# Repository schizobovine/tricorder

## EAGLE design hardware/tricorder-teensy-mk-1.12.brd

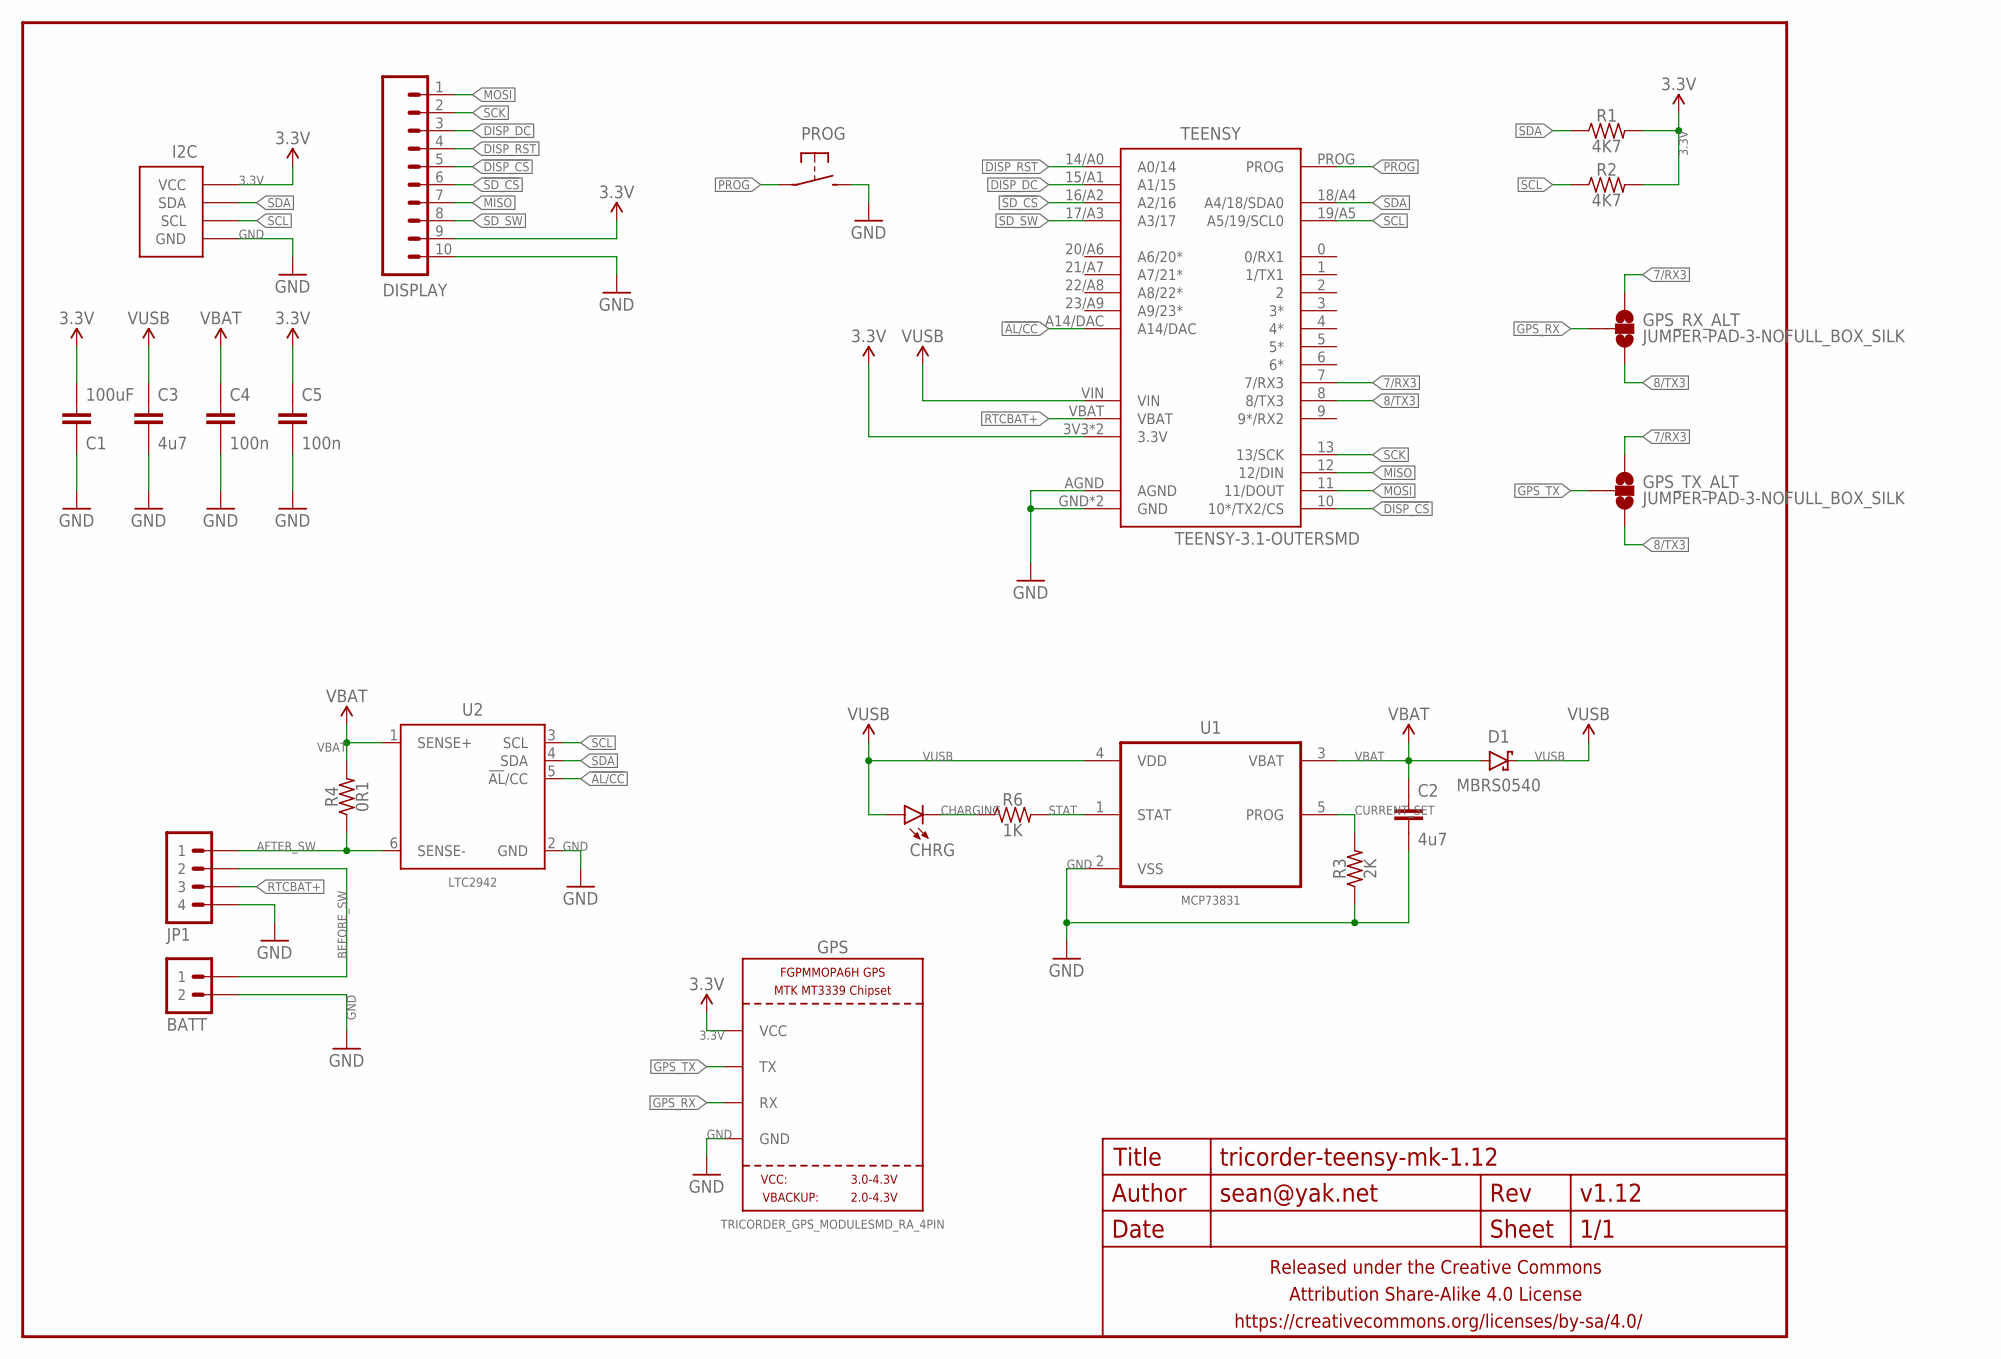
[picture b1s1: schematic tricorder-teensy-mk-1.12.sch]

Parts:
BATT: M02JST-2MM-SMT; JST-2-SMD
C1: 100uF; C1210
C2, C3: 4u7; C0603-TIGHTER
C4, C5: 100n; C0603-TIGHTER
CHRG: LED0603-TIGHT; LED-0603-TIGHT
D1: MBRS0540; SOD123-SCHOTTKY
DISPLAY: M10SMD_RA_2MM; 1X10_SMD_RA_MALE
FRAME1: FRAME-LETTERNO_PACKAGE; DUMMY
GPS: TRICORDER_GPS_MODULESMD_RA_4PIN; TRICORDER_GPS_MODULE_RA_CONN_SMD_4PIN
GPS_RX_ALT: JUMPER-PAD-3-NOFULL_BOX_SILK; PAD-JUMPER-3-NO_YES_SILK_FULL_BOX
GPS_TX_ALT: JUMPER-PAD-3-NOFULL_BOX_SILK; PAD-JUMPER-3-NO_YES_SILK_FULL_BOX
I2C: M04-I2CSMD_2MM_RA; 1X04_SMD_RA_2MM_I2C
JP1: M04SMD_RA_2MM; 1X04_SMD_RA_2MM
PROG: SPST-NO-TACTCK-PTS840-GK; TACTILE-SMD-CK-PTS840-GK
R1, R2: 4K7; R0603-TIGHTER
R3: 2K; R0603-TIGHTER
R4: 0R1; R0805-TIGHTER
R6: 1K; R0603-TIGHTER
TEENSY: TEENSY-3.1-OUTERSMD; TEENSY-3.1_SMT_BOTTOM_OUTERONLY
U1: MCP73831; SOT95P280X145-5N
U2: LTC2942; DFN200X300X50-7N

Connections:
3.3V: C1.2, C5.1, DISPLAY.9, GPS.VCC, I2C.VCC, R1.2, R2.2, TEENSY.3V3 (3.3V), TEENSY.3V3@1 (3.3V)
7/RX3: GPS_RX_ALT.1, GPS_TX_ALT.1, TEENSY.7 (7/RX3)
8/TX3: GPS_RX_ALT.3, GPS_TX_ALT.3, TEENSY.8 (8/TX3)
!AL/CC: TEENSY.A14/DAC, U2.5 (!AL!/CC)
!DISP_CS: DISPLAY.5, TEENSY.10 (10*/TX2/CS)
!SD_CS: DISPLAY.6, TEENSY.16/A2 (A2/16)
AFTER_SW: JP1.1, R4.1, U2.6 (SENSE-)
BEFORE_SW: BATT.2 (1), JP1.2
CHARGING: CHRG.C, R6.1
CURRENT_SET: R3.2, U1.5 (PROG)
DISP_DC: DISPLAY.3, TEENSY.15/A1 (A1/15)
DISP_RST: DISPLAY.4, TEENSY.14/A0 (A0/14)
GND: BATT.1 (2), C1.1, C2.2, C3.2, C4.2, C5.2, DISPLAY.10, GPS.GND, I2C.GND, JP1.4, PROG.3 (2), PROG.4 (2), R3.1, TEENSY.AGND, TEENSY.GND, TEENSY.GND@1 (GND), U1.2 (VSS), U2.2 (GND)
GPS_RX: GPS.RX, GPS_RX_ALT.2
GPS_TX: GPS.TX, GPS_TX_ALT.2
MISO: DISPLAY.7, TEENSY.12 (12/DIN)
MOSI: DISPLAY.1, TEENSY.11 (11/DOUT)
PROG: PROG.1, PROG.2 (1), TEENSY.PROG
RTCBAT+: JP1.3, TEENSY.VBAT
SCK: DISPLAY.2, TEENSY.13 (13/SCK)
SCL: I2C.SCL, R2.1, TEENSY.19/A5 (A5/19/SCL0), U2.3 (SCL)
SDA: I2C.SDA, R1.1, TEENSY.18/A4 (A4/18/SDA0), U2.4 (SDA)
SD_SW: DISPLAY.8, TEENSY.17/A3 (A3/17)
STAT: R6.2, U1.1 (STAT)
VBAT: C2.1, C4.1, D1.A, R4.2, U1.3 (VBAT), U2.1 (SENSE+)
VUSB: C3.1, CHRG.A, D1.C, TEENSY.VIN, U1.4 (VDD)

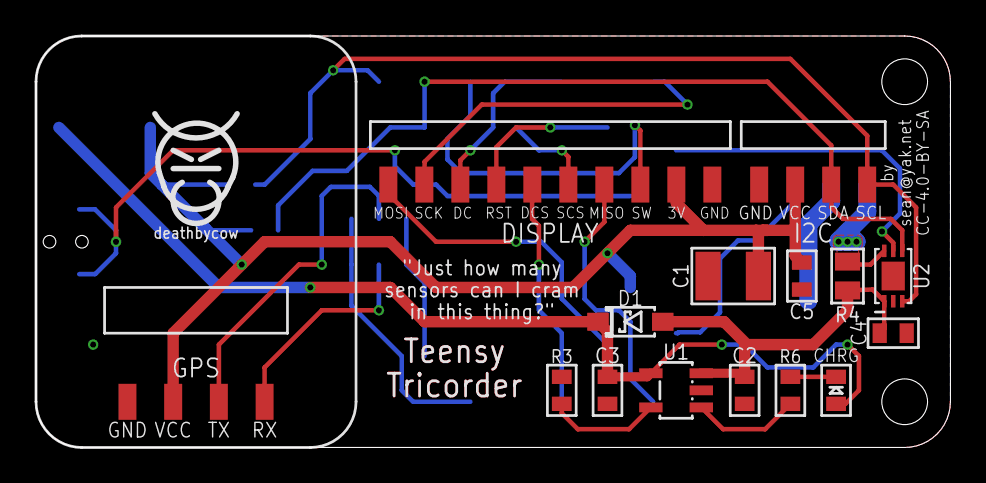
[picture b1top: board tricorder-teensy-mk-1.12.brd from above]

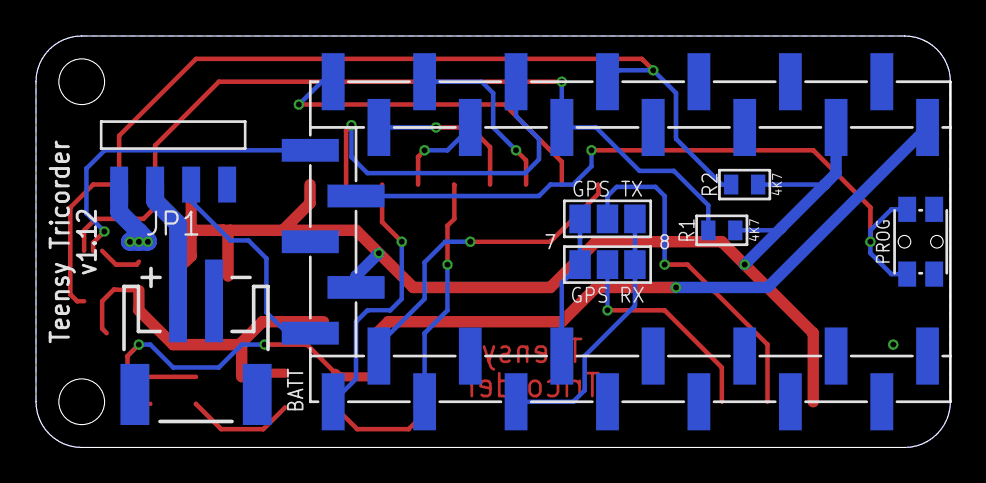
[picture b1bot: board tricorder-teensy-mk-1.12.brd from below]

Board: 2 copper layers, 50.8 x 22.9 mm, 25 parts (7 on the bottom side), 26 nets.

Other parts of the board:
U$1: COW_SMALL

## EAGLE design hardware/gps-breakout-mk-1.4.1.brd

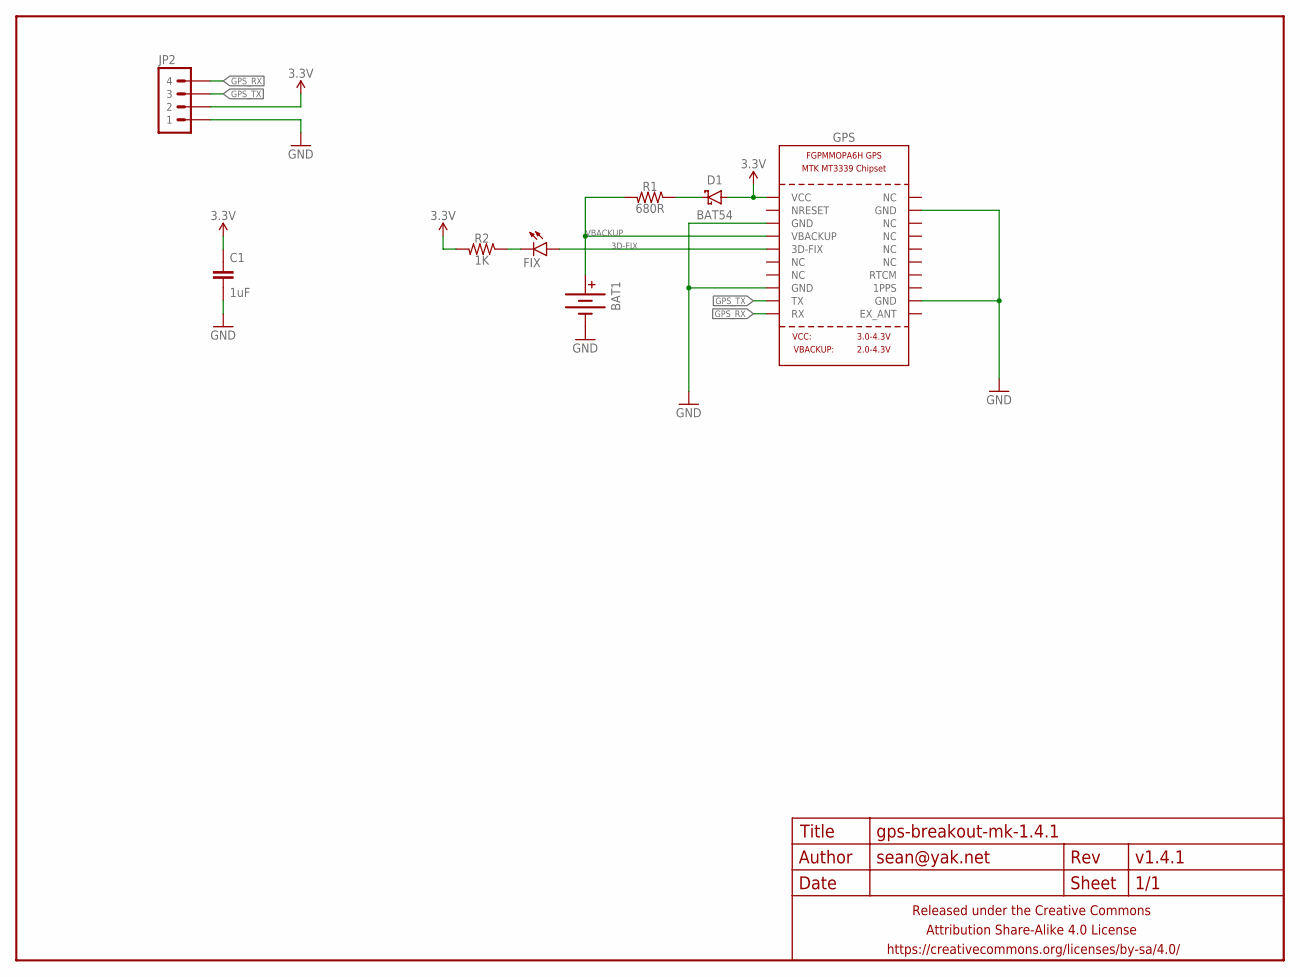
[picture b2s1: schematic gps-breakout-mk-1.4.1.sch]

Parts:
BAT1: BATTERYML414; BATTCON_4.8MM
C1: 1uF; C0603-TIGHTER
D1: BAT54; SOD323-SCHOTTKY
FIX: LED0603-TIGHT; LED-0603-TIGHT
FRAME1: FRAME-LETTERNO_PACKAGE; DUMMY
GPS: GPS_FGPMMOPA6H; FGPMMOPA6H
JP2: M04SMD-FEMALE-DUAL; 1X04-SMD-FEMALE-RA-DUAL
R1: 680R; R0603-TIGHTER
R2: 1K; R0603-TIGHTER

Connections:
3.3V: C1.1, D1.A, GPS.P$1 (VCC), JP2.P$2 (2), JP2.P$2_1 (2), R2.2
3D-FIX: FIX.A, GPS.P$5 (3D-FIX)
GND: BAT1.-, C1.2, GPS.P$3 (GND), GPS.P$8 (GND), GPS.P$12 (GND), GPS.P$19 (GND), JP2.P$1 (1), JP2.P$1_1 (1)
GPS_RX: GPS.P$10 (RX), JP2.P$4 (4), JP2.P$4_1 (4)
GPS_TX: GPS.P$9 (TX), JP2.P$3 (3), JP2.P$3_1 (3)
unnamed: D1.C, R1.1
unnamed: FIX.C, R2.1
VBACKUP: BAT1.A1 (+), BAT1.A2 (+), GPS.P$4 (VBACKUP), R1.2

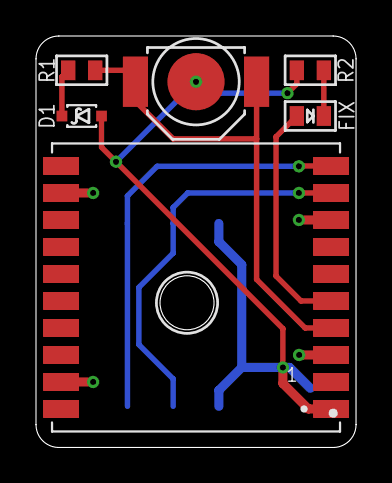
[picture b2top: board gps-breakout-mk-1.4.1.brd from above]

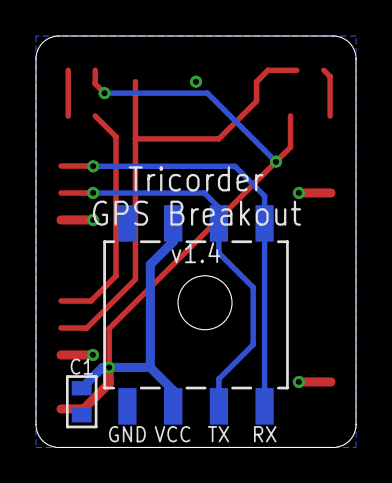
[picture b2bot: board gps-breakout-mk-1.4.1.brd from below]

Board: 2 copper layers, 17.8 x 22.9 mm, 9 parts (2 on the bottom side), 8 nets.

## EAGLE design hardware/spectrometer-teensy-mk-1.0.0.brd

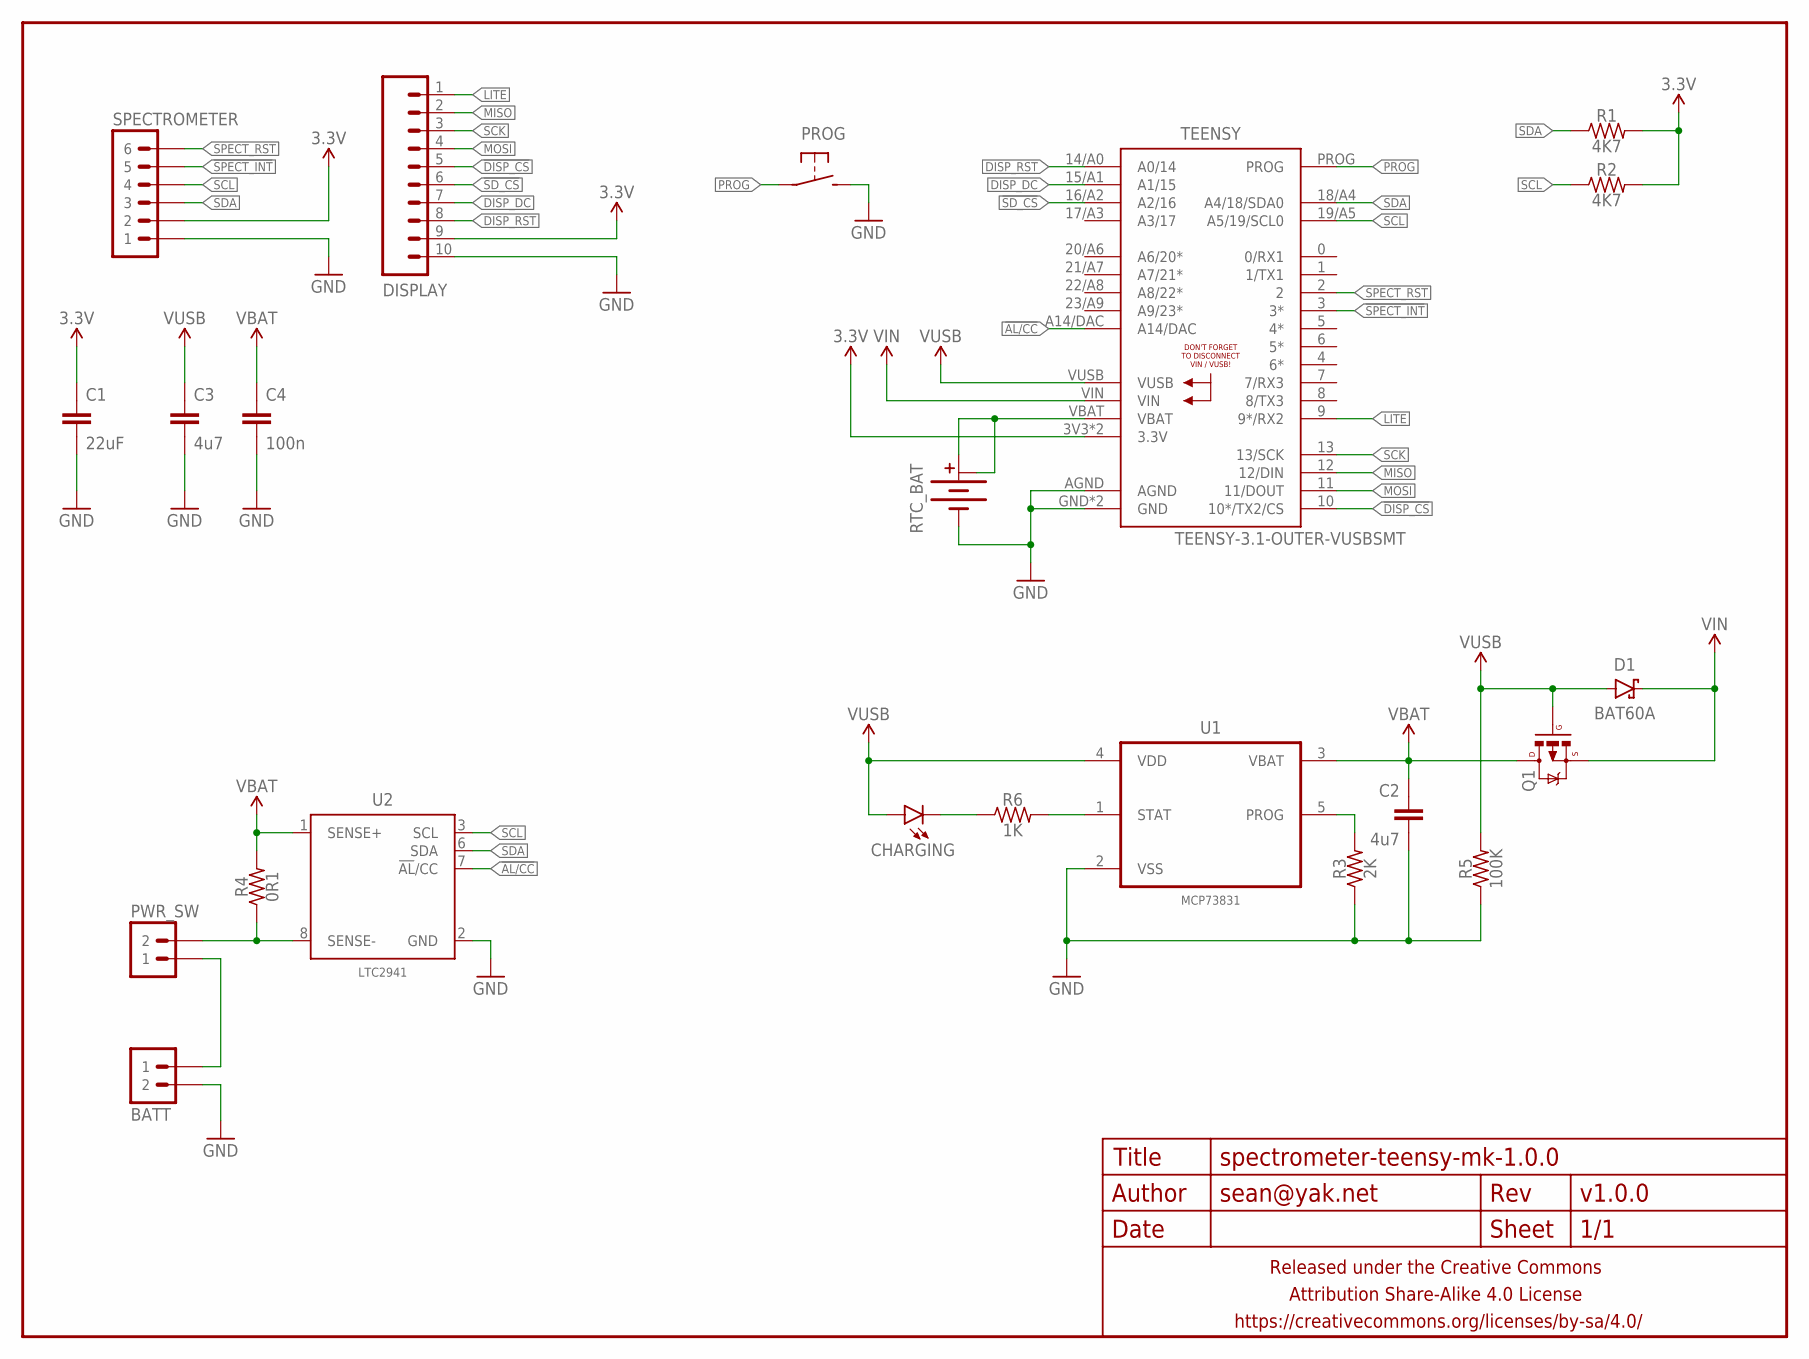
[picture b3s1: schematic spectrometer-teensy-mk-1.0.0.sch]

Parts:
BATT: M02JST-2MM-SMT; JST-2-SMD
C1: 22uF; C0805-TIGHTER
C2, C3: 4u7; C0603-TIGHTER
C4: 100n; C0603-TIGHTER
CHARGING: LED0603-TIGHT; LED-0603-TIGHT
D1: BAT60A; SOD123-SCHOTTKY
DISPLAY: M10SMD_RA_2MM; 1X10_SMD_RA_MALE
FRAME1: FRAME-LETTERNO_PACKAGE; DUMMY
PROG: SPST-NO-TACTCK-PTS840-GK; TACTILE-SMD-CK-PTS840-GK
PWR_SW: M02JST-2MM-SMT; JST-2-SMD
Q1: MOSFET-PCHANNELSOT-23; SOT23
R1, R2: 4K7; R0603-TIGHTER
R3: 2K; R0603-TIGHTER
R4: 0R1; R0603-TIGHTER
R5: 100K; R0603-TIGHTER
R6: 1K; R0603-TIGHTER
RTC_BAT: BATTERY-COINCR1225_SMD_SMALLER; BATTCON_12MM_SMD
SPECTROMETER: M06SMD-2MM-RA; 1X06_SMD_RA_2MM
TEENSY: TEENSY-3.1-OUTER-VUSBSMT; TEENSY-3.1_SMT_BOTTOM_OUTERMOSTLY_VUSB
U1: MCP73831; SOT95P280X145-5N
U2: LTC2941; MSOP-8

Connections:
3.3V: C1.1, DISPLAY.9, R1.2, R2.2, SPECTROMETER.2, TEENSY.3V3 (3.3V), TEENSY.3V3@1 (3.3V)
!AL/CC: TEENSY.A14/DAC, U2.7 (!AL!/CC)
!DISP_CS: DISPLAY.5, TEENSY.10 (10*/TX2/CS)
!SD_CS: DISPLAY.6, TEENSY.16/A2 (A2/16)
!SPECT_INT: SPECTROMETER.5, TEENSY.3 (3*)
DISP_DC: DISPLAY.7, TEENSY.15/A1 (A1/15)
DISP_RST: DISPLAY.8, TEENSY.14/A0 (A0/14)
GND: BATT.1 (2), C1.2, C2.2, C3.2, C4.2, DISPLAY.10, PROG.3 (2), PROG.4 (2), R3.1, R5.1, RTC_BAT.-, SPECTROMETER.1, TEENSY.AGND, TEENSY.GND, TEENSY.GND@1 (GND), U1.2 (VSS), U2.2 (GND)
LITE: DISPLAY.1, TEENSY.9 (9*/RX2)
MISO: DISPLAY.2, TEENSY.12 (12/DIN)
MOSI: DISPLAY.4, TEENSY.11 (11/DOUT)
unnamed: R6.2, U1.1 (STAT)
unnamed: CHARGING.C, R6.1
unnamed: BATT.2 (1), PWR_SW.2 (1)
unnamed: R3.2, U1.5 (PROG)
unnamed: PWR_SW.1 (2), R4.1, U2.8 (SENSE-)
unnamed: RTC_BAT.+@1 (+), RTC_BAT.+@2 (+1), TEENSY.VBAT
PROG: PROG.1, PROG.2 (1), TEENSY.PROG
SCK: DISPLAY.3, TEENSY.13 (13/SCK)
SCL: R2.1, SPECTROMETER.4, TEENSY.19/A5 (A5/19/SCL0), U2.3 (SCL)
SDA: R1.1, SPECTROMETER.3, TEENSY.18/A4 (A4/18/SDA0), U2.6 (SDA)
SPECT_RST: SPECTROMETER.6, TEENSY.2
VBAT: C2.1, C4.1, Q1.3 (D), R4.2, U1.3 (VBAT), U2.1 (SENSE+)
VIN: D1.C, Q1.2 (S), TEENSY.VIN
VUSB: C3.1, CHARGING.A, D1.A, Q1.1 (G), R5.2, TEENSY.VUSB, U1.4 (VDD)

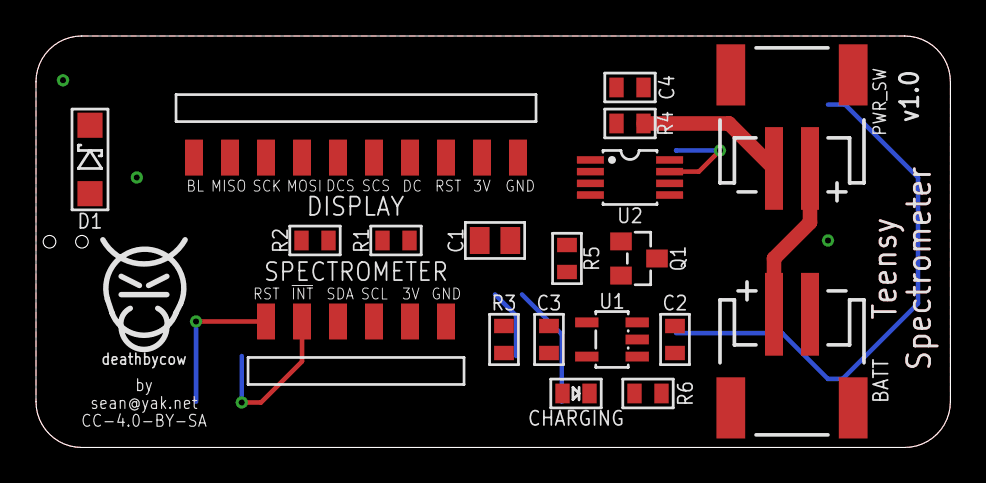
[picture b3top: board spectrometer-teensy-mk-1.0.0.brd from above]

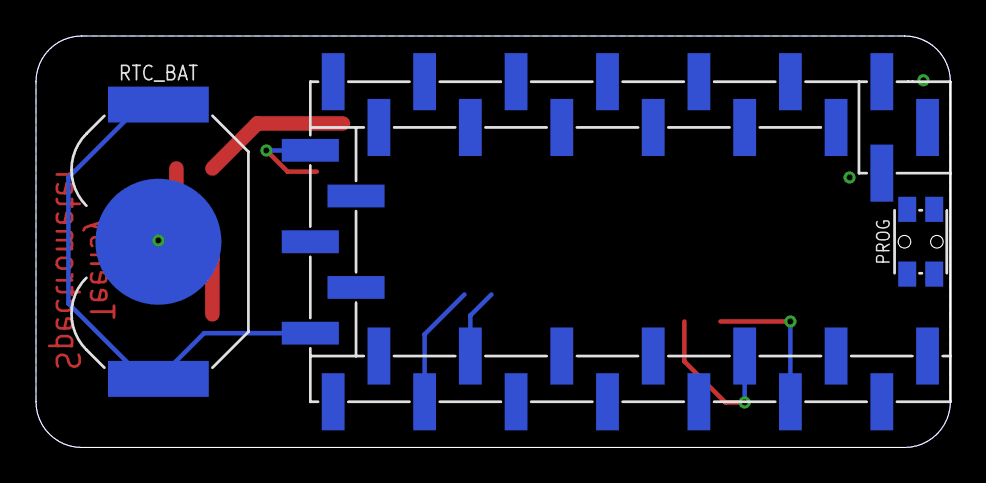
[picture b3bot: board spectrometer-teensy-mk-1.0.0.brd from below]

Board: 2 copper layers, 50.8 x 22.9 mm, 24 parts (2 on the bottom side), 25 nets.

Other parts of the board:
U$1: COW_SMALL

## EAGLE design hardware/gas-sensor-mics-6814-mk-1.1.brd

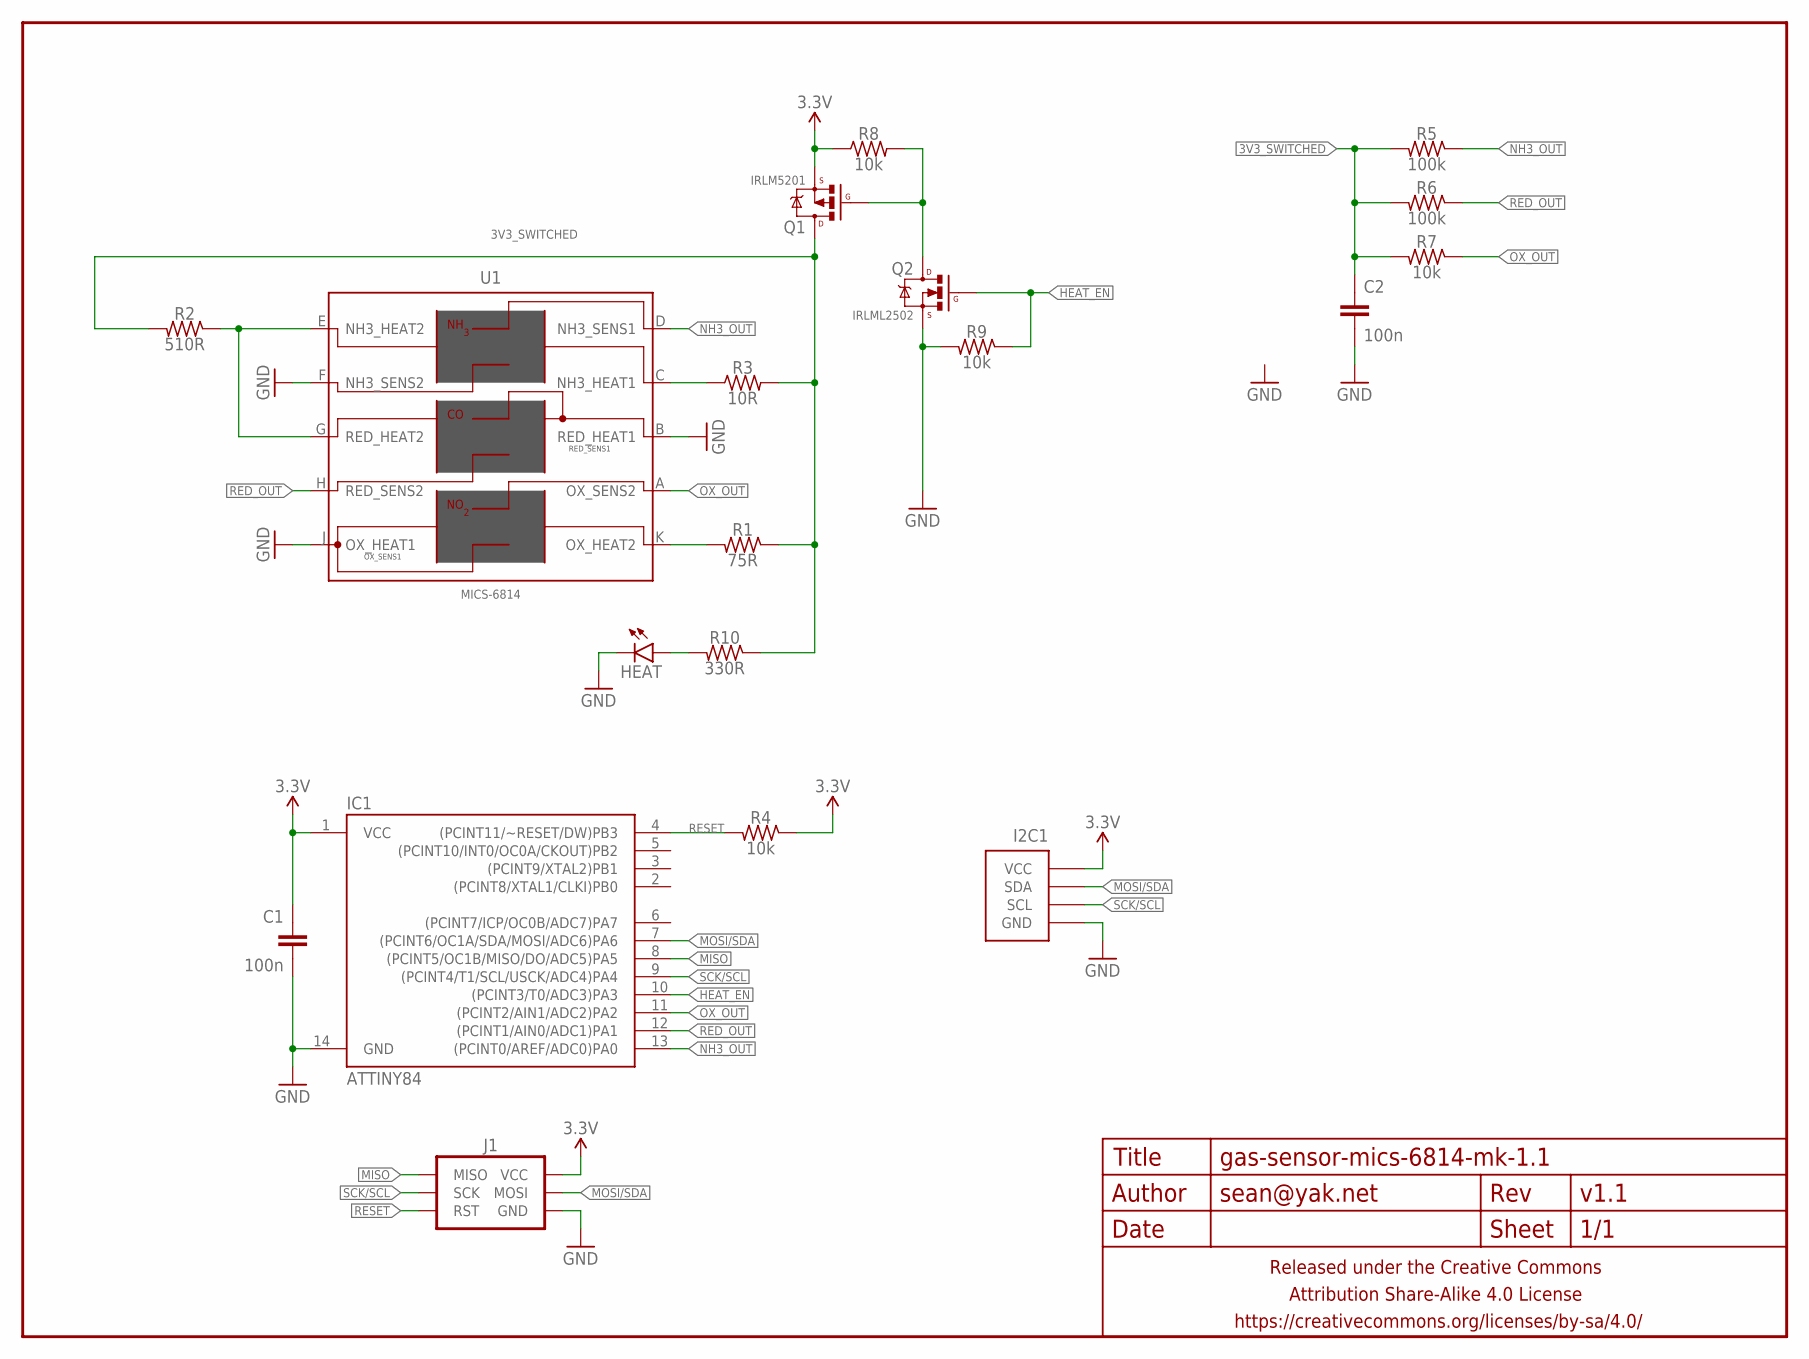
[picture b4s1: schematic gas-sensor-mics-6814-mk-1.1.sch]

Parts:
C1, C2: 100n; C0603-TIGHTER
FRAME1: FRAME-LETTERNO_PACKAGE; DUMMY
HEAT: LED0603-TIGHT; LED-0603-TIGHT
I2C1: M04-I2CPTH-0.1IN-CENTERED; 1X04-PTH-VERT-I2C-CENTERED
IC1: ATTINY84; SO14
J1: AVR_SPI_PRG_6SMD_TEST_POINTS; 2X3_SMD_TEST_POINTS
Q1: IRLM5201; SOT23
Q2: IRLML2502; SOT23
R1: 75R; R0603-TIGHTER
R2: 510R; R0603-TIGHTER
R3: 10R; R0603-TIGHTER
R4, R7, R8, R9: 10k; R0603-TIGHTER
R5, R6: 100k; R0603-TIGHTER
R10: 330R; R0603-TIGHTER
U1: MICS-6814; MICS-10-PIN

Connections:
3.3V: C1.1, I2C1.VCC, IC1.1 (VCC), J1.2 (VCC), Q1.2 (S), R4.1, R8.1
3V3_SWITCHED: C2.1, Q1.3 (D), R1.1, R2.2, R3.2, R5.2, R6.2, R7.2, R10.1
GND: C1.2, C2.2, HEAT.C, I2C1.GND, IC1.14 (GND), J1.6 (GND), Q2.2 (S), R9.2, U1.B (RED_HEAT1), U1.F (NH3_SENS2), U1.J (OX_HEAT1)
HEAT_EN: IC1.10 ((PCINT3/T0/ADC3)PA3), Q2.1 (G), R9.1
MISO: IC1.8 ((PCINT5/OC1B/MISO/DO/ADC5)PA5), J1.1 (MISO)
MOSI/SDA: I2C1.SDA, IC1.7 ((PCINT6/OC1A/SDA/MOSI/ADC6)PA6), J1.4 (MOSI)
unnamed: R2.1, U1.E (NH3_HEAT2), U1.G (RED_HEAT2)
unnamed: R1.2, U1.K (OX_HEAT2)
unnamed: R3.1, U1.C (NH3_HEAT1)
unnamed: Q1.1 (G), Q2.3 (D), R8.2
unnamed: HEAT.A, R10.2
NH3_OUT: IC1.13 ((PCINT0/AREF/ADC0)PA0), R5.1, U1.D (NH3_SENS1)
OX_OUT: IC1.11 ((PCINT2/AIN1/ADC2)PA2), R7.1, U1.A (OX_SENS2)
RED_OUT: IC1.12 ((PCINT1/AIN0/ADC1)PA1), R6.1, U1.H (RED_SENS2)
RESET: IC1.4 ((PCINT11/~RESET/DW)PB3), J1.5 (RST), R4.2
SCK/SCL: I2C1.SCL, IC1.9 ((PCINT4/T1/SCL/USCK/ADC4)PA4), J1.3 (SCK)

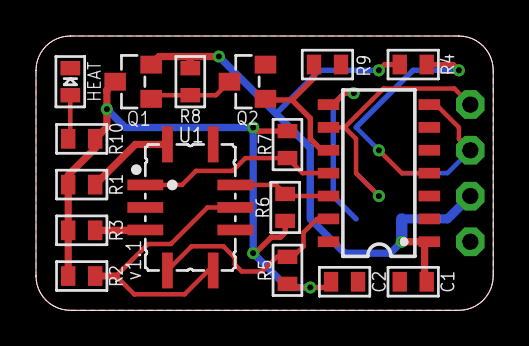
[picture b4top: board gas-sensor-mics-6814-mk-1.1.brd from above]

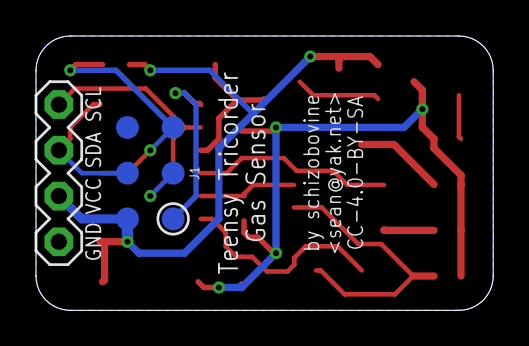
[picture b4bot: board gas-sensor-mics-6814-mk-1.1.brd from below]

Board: 2 copper layers, 25.4 x 15.2 mm, 20 parts (2 on the bottom side), 16 nets.

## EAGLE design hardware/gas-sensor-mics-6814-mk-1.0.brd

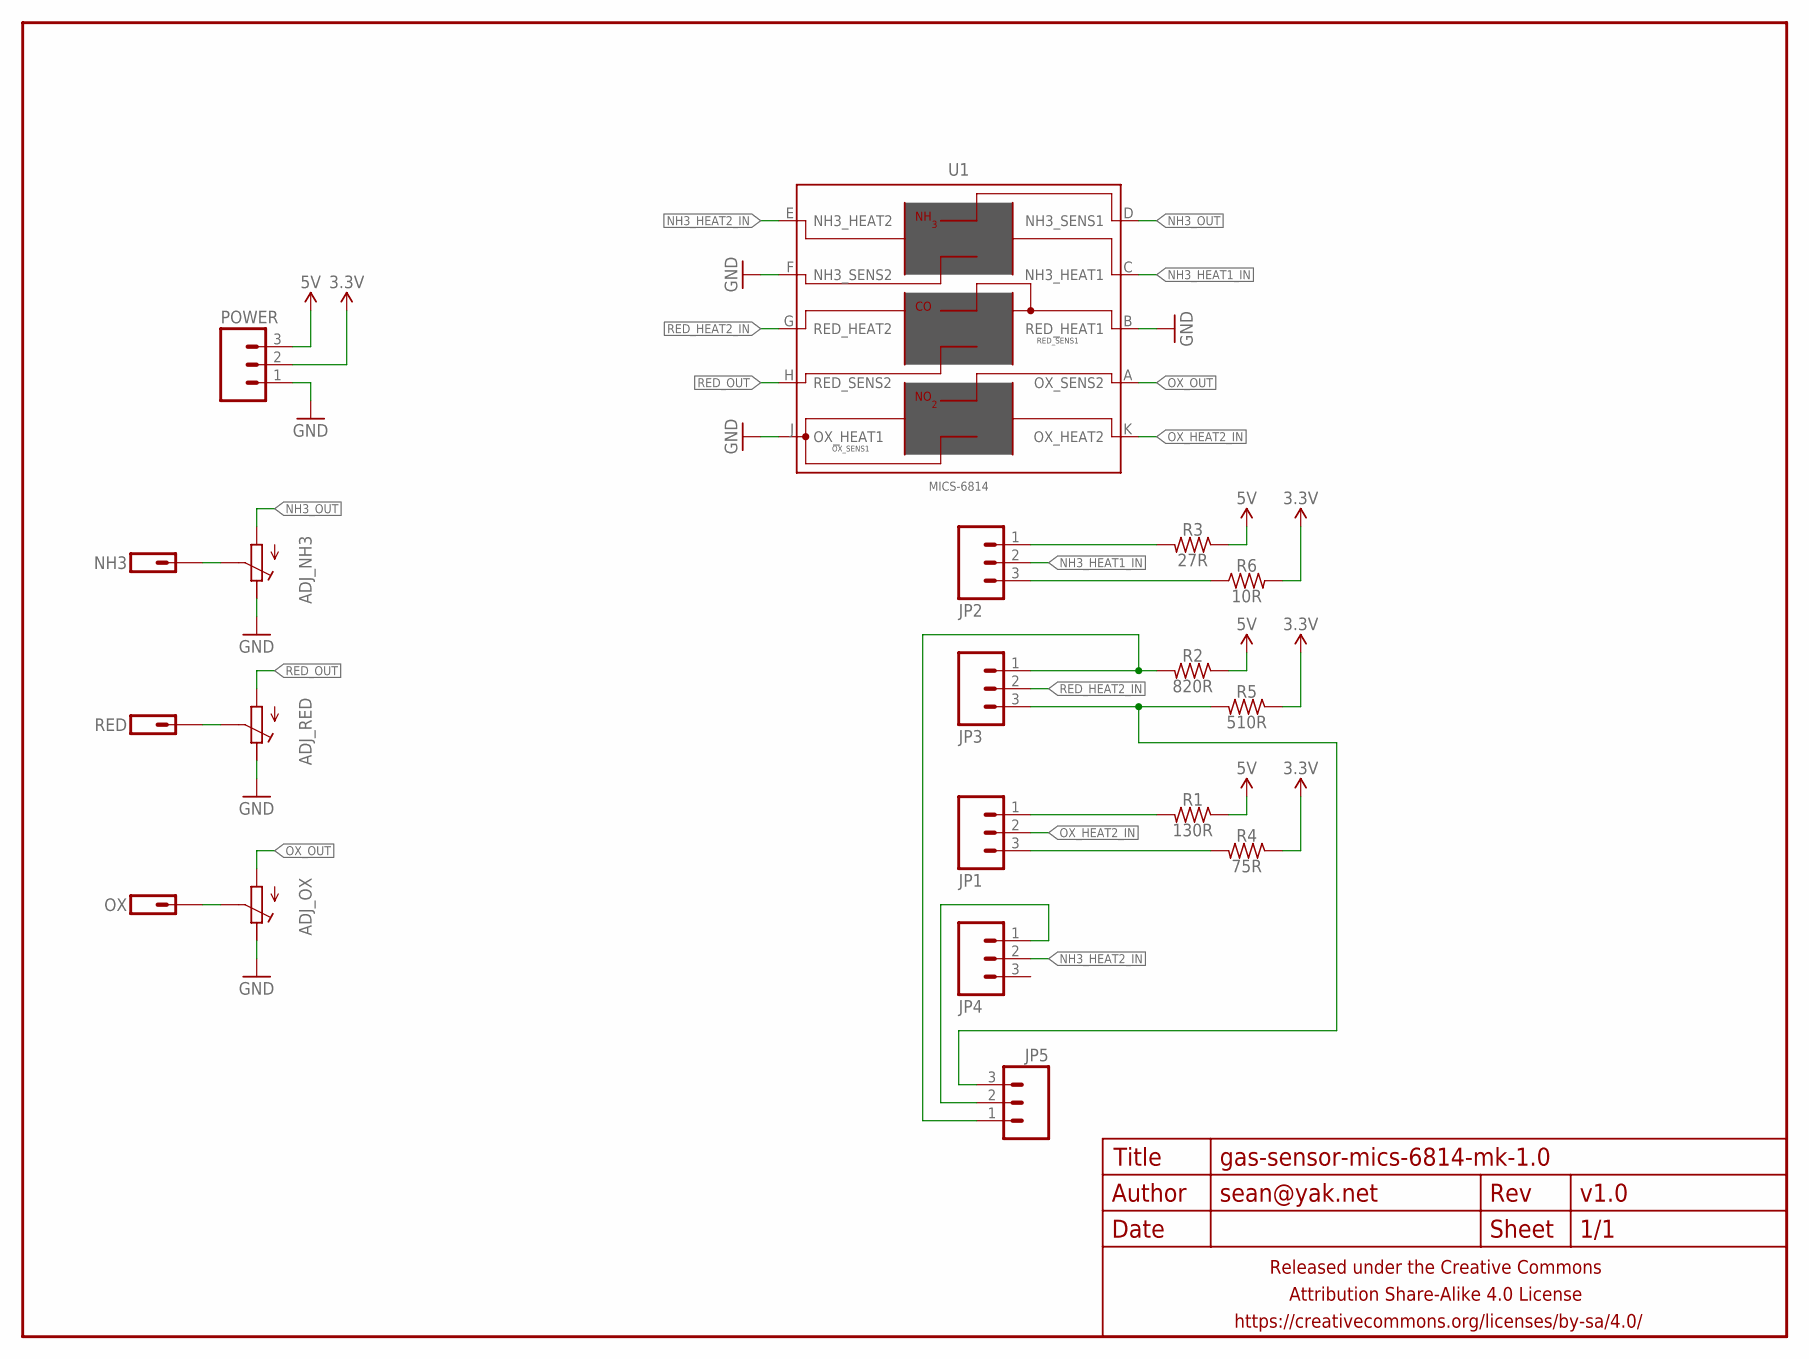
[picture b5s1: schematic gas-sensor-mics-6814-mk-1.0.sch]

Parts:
ADJ_NH3: POTENTIOMETEREVM3Y; EVM3Y
ADJ_OX: POTENTIOMETEREVM3Y; EVM3Y
ADJ_RED: POTENTIOMETEREVM3Y; EVM3Y
FRAME1: FRAME-LETTERNO_PACKAGE; DUMMY
JP1, JP2, JP3, JP4, JP5: M03PTH-CENTERED; 1X03-CENTERED
NH3: M01PTH-2MM-OFFSET; 1X01_2MM_OFFSET
OX: M01PTH-2MM-OFFSET; 1X01_2MM_OFFSET
POWER: M03PTH-CENTERED; 1X03-CENTERED
R1: 130R; R0603-TIGHTER
R2: 820R; R0603-TIGHTER
R3: 27R; R0603-TIGHTER
R4: 75R; R0603-TIGHTER
R5: 510R; R0603-TIGHTER
R6: 10R; R0603-TIGHTER
RED: M01PTH-2MM-OFFSET; 1X01_2MM_OFFSET
U1: MICS-6814; MICS-10-PIN

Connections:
3.3V: POWER.2, R4.1, R5.1, R6.2
5V: POWER.3, R1.1, R2.1, R3.1
GND: ADJ_NH3.E, ADJ_OX.E, ADJ_RED.E, POWER.1, U1.B (RED_HEAT1), U1.F (NH3_SENS2), U1.J (OX_HEAT1)
unnamed: JP2.1, R3.2
unnamed: ADJ_NH3.S, NH3.1
unnamed: ADJ_RED.S, RED.1
unnamed: ADJ_OX.S, OX.1
unnamed: JP1.1, R1.2
unnamed: JP1.3, R4.2
unnamed: JP2.3, R6.1
unnamed: JP3.3, JP5.3, R5.2
unnamed: JP3.1, JP5.1, R2.2
unnamed: JP4.1, JP5.2
NH3_HEAT1_IN: JP2.2, U1.C (NH3_HEAT1)
NH3_HEAT2_IN: JP4.2, U1.E (NH3_HEAT2)
NH3_OUT: ADJ_NH3.A, U1.D (NH3_SENS1)
OX_HEAT2_IN: JP1.2, U1.K (OX_HEAT2)
OX_OUT: ADJ_OX.A, U1.A (OX_SENS2)
RED_HEAT2_IN: JP3.2, U1.G (RED_HEAT2)
RED_OUT: ADJ_RED.A, U1.H (RED_SENS2)

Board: 2 copper layers, 20 parts (0 on the bottom side), 20 nets, no tracks yet.

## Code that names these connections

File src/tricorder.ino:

/*
 * tricorder.ino
 *
 * Adafruit Feather-based, Bluetooth-enabled sensor thingy.
 *
 * Author: Sean Caulfield <sean@yak.net>
 * License: GPL v2.0
 *
 */

#include <Arduino.h>
#include <SPI.h>
#include <Wire.h>
#include <SD.h>

#include <Adafruit_GFX.h>
#include <Adafruit_SSD1351.h>
#include <Adafruit_BLE.h>
#include <Adafruit_BluefruitLE_SPI.h>

#include <Adafruit_Sensor.h>
#include <Adafruit_BMP280.h>
#include <Adafruit_BNO055.h>
#include <Adafruit_MLX90614.h>
#include <Adafruit_SHT31.h>
#include <Adafruit_TCS34725.h>
#include <Adafruit_TSL2591.h>
#include <Adafruit_VEML6070.h>

#define BATT_DIV_PIN   A7

#define SD_CARDDETECT  A1
#define SD_CS          A2

#define DISP_CS        A3
#define DISP_DC        A4
#define DISP_RST       A5

#define BLE_CS         8
#define BLE_IRQ        7
#define BLE_RST        4

#define DEFAULT_PRESSURE 1000.0
#define LOG_FILE_NAME "data.log"

#define PRINT(...) do { \
    Serial.print(__VA_ARGS__); \
    ble.print(__VA_ARGS__); \
    if (logFile) { logFile.print(__VA_ARGS__); } \
  } while (0);

#define PRINTLN(...) do { \
    Serial.println(__VA_ARGS__); \
    ble.println(__VA_ARGS__); \
    if (logFile) { logFile.println(__VA_ARGS__); } \
  } while (0);

////////////////////////////////////////////////////////////////////////
// GLOBAL OBJECTS
////////////////////////////////////////////////////////////////////////

Adafruit_SSD1351 display = Adafruit_SSD1351(DISP_CS, DISP_DC, DISP_RST);

Adafruit_BluefruitLE_SPI ble(BLE_CS, BLE_IRQ, BLE_RST);

Adafruit_BMP280 bmp280;
Adafruit_BNO055 bno055;
Adafruit_MLX90614 mlx90614;
Adafruit_SHT31 sht31;
Adafruit_TCS34725 tcs34725;
Adafruit_TSL2591 tsl2591;
Adafruit_VEML6070 veml6070;

File logFile;

////////////////////////////////////////////////////////////////////////
// HALPING
////////////////////////////////////////////////////////////////////////

float getBattVoltage() {
  float measured = analogRead(BATT_DIV_PIN);
  return measured * 2.0 * 3.3 / 1024;
}

////////////////////////////////////////////////////////////////////////
// SETUP
////////////////////////////////////////////////////////////////////////

void setup() {

  // Maybe the display is being dumb and not replying fast enough?
  delay(200);
  
  // Init i2C
  Wire.begin();

  // Init display

  // Init sensors
  bmp280.begin();
  bno055.begin();
  mlx90614.begin();
  sht31.begin();
  tcs34725.begin();
  tsl2591.begin();
  veml6070.begin(VEML6070_1_T);

  // Init serial for debugging BLE modem
  while (!Serial)
    delay(1);
  Serial.begin(115200);
  Serial.println("HAI");

  // Initialize BLE modem
  ble.begin(true);
  ble.echo(false);
  ble.info();

  // Open log on SD card if present
  pinMode(SD_CARDDETECT, INPUT_PULLUP);
  if (digitalRead(SD_CARDDETECT)) {
    if (!SD.begin(SD_CS)) {
      PRINTLN("No SD card, disabling log");
    } else {
      logFile = SD.open(LOG_FILE_NAME, FILE_WRITE);
    }
  }

  // For zee debugging
  pinMode(13, OUTPUT);

}

////////////////////////////////////////////////////////////////////////
// MAIN LOOP
////////////////////////////////////////////////////////////////////////

void loop() {

  // START DEBUG CRAP

  digitalWrite(13, HIGH);
  delay(500);
  digitalWrite(13, LOW);
  delay(500);

  uint32_t now = millis();
  Serial.println(now);

  // END DEBUG CRAP

  float bmp280_temp = bmp280.readTemperature();
  float press = bmp280.readPressure();
  float alt = bmp280.readAltitude(DEFAULT_PRESSURE);

  PRINTLN("BMP280");
  PRINT("T   = "); PRINTLN(bmp280_temp);
  PRINT("P   = "); PRINT(press); PRINTLN("Pa");
  PRINT("Alt = "); PRINT(alt); PRINTLN("m");

  imu::Vector<3> euler = bno055.getVector(Adafruit_BNO055::VECTOR_EULER);
  float x = euler.x();
  float y = euler.y();
  float z = euler.z();
  uint8_t cal_sys, cal_gyro, cal_acc, cal_mag;
  bno055.getCalibration(&cal_sys, &cal_gyro, &cal_acc, &cal_mag);

  PRINTLN("BNO055");
  PRINT("X = "); PRINTLN(x);
  PRINT("Y = "); PRINTLN(y);
  PRINT("Z = "); PRINTLN(z);
  PRINT("Calibration (Sys)  = "); PRINTLN(cal_sys);
  PRINT("Calibration (Gyro) = "); PRINTLN(cal_gyro);
  PRINT("Calibration (Acc)  = "); PRINTLN(cal_acc);
  PRINT("Calibration (Mag)  = "); PRINTLN(cal_mag);

  float ir_amb_c = mlx90614.readAmbientTempC();
  float ir_amb_f = mlx90614.readAmbientTempF();
  float ir_obj_c = mlx90614.readObjectTempC();
  float ir_obj_f = mlx90614.readObjectTempF();

  PRINTLN("MLX90614");
  PRINT("Ambient = "); PRINT(ir_amb_c); PRINTLN("C");
  PRINT("          "); PRINT(ir_amb_f); PRINTLN("F");
  PRINT("Object  = "); PRINT(ir_obj_c); PRINTLN("C");
  PRINT("          "); PRINT(ir_obj_f); PRINTLN("F");

  float sht31_temp = sht31.readTemperature();
  float humidity = sht31.readHumidity();

  PRINTLN("SHT31");
  PRINT("T = "); PRINTLN(sht31_temp);
  PRINT("RH% = "); PRINTLN(humidity);

  uint16_t r, g, b, c;
  tcs34725.getRawData(&r, &g, &b, &c);
  uint16_t colorTemp = tcs34725.calculateColorTemperature(r, g, b);
  uint16_t lux = tcs34725.calculateLux(r, g, b);

  PRINTLN("TCS34725");
  PRINT("R = "); PRINTLN(r);
  PRINT("G = "); PRINTLN(g);
  PRINT("B = "); PRINTLN(b);
  PRINT("C = "); PRINTLN(c);
  PRINT("Color Temp = "); PRINTLN(colorTemp);
  PRINT("Lux = "); PRINTLN(lux);

  uint16_t vis = tsl2591.getLuminosity(TSL2591_VISIBLE);
  uint16_t ir = tsl2591.getLuminosity(TSL2591_INFRARED);

  PRINTLN("TSL2591");

  float uv = veml6070.readUV();

  PRINTLN("VEML6070");
  PRINT("UV = "); PRINTLN(uv);

  delay(1000);

}

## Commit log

2015-12-16 modules like whoa
2015-12-16 right display size whoops
2016-01-10 adding makefile though not working yet
2016-01-10 license GPLv2
2016-01-10 alsdkfjaldsj
2016-01-10 add ALL THE LIBRARIES
2016-01-10 somewhat doing interesting things now
2016-01-10 adding IR temp sensor and RGB color sensor libraries
2016-01-10 adding libs to makefile, reorg display, ignore build dirs
2016-01-11 adding BLE modem submodule
2016-01-11 blow away UART
2016-01-11 added modem, no longer fits on fucking board. YAAAAY >_<
2016-01-12 purge Adafruit_Sensor submodule
2016-01-12 update with sensor removal changes
2016-01-12 more Adafruit_Sensor purging
2016-01-12 remove final bits of Adafruit_Sensor code
2016-05-25 display on
2016-05-25 Remove unused submodules, add color OLED lib
2016-05-25 adding various submodules/libs
2016-05-26 tinkering
2016-05-26 dumping makefile for arduino-builder
2016-05-26 strip out bs for simple testing
2016-05-26 attempt to use this thing sanely
2016-05-26 need to fork this b/c includes are HARD
2016-05-26 add my own forked copy
2016-05-26 move header files
2016-05-26 lasdkjfadsj
2016-05-26 FORK THIS
2016-05-26 fully forked
2016-05-26 auuugH
2016-05-26 moving to src fixes build issues. wat.
2016-05-26 revert lib changes by moving to src subdir
2016-05-27 make building work for reals
2016-05-27 it compiles!
2016-05-27 well ble compiles now
2016-05-27 OLED lib now compiling
2016-05-27 add SHT31 lib
2016-05-27 all libs included now?
2016-05-27 now reading from all sensors
2016-05-27 dump sensor data to serial
2016-05-27 macros to simult dump to ble and serial
2016-05-28 sd logging; all as yet untested
2016-06-02 repo restructuring
2016-06-02 first gen purpose photodiode sensor board
2016-06-02 from the uv meter project
2016-06-02 quad opamps
2016-06-04 initial layout tomfoolery
2016-06-04 testing board pre layout
2016-06-06 more photodiode dickery
2016-06-09 adding IR sensor and forward light sensor PCBs
2016-06-09 initial revision for gas sensor board
2016-06-11 connector board
2016-06-13 connector board markup?
2016-06-13 second version, diff connectors/layout
2016-06-13 third version, yet different connectors
2016-06-20 minor tweaks to layout but not done
2016-06-20 using jst connectors now
2016-06-21 more layout playing around for the jst version
2016-06-28 another version of the photodiode testing board
2016-06-28 library wankery
2016-06-28 jst version off to fab
2016-06-28 initial work on front-end board for the light sensors
2016-06-29 submodule path screwed up
2016-06-30 new software for new hardware
2016-06-30 blow away the submodules and re-add
2016-06-30 readd all the submodules
2016-06-30 move v1 to its own subfolder
2016-06-30 rename to distinguish when symlinking to sketchbooK
2016-06-30 remove submodules from v2 code bc submodules suck
2016-06-30 rename v2 to distinguish when symlinking
2016-07-01 version 2 now displaying UV readings
2016-07-03 adding in temp/humidity lib
2016-07-03 move this out of the way to be less confusing plus is also useful to multiple revs maybe
2016-07-04 wip display routines
2016-07-04 displaying more data still wip
2016-07-05 center title
2016-07-05 new front end board wip
2016-07-28 many new sensor boards
2016-07-29 relaid out, different set of sensors
2016-08-01 new panelized sensor boards
2016-08-03 swap apds9250 for tcs3400
2016-08-03 rotate gps breakout 90deg
2016-08-03 wtf how did this not get checked in
2016-08-20 first revision on gps module board
2016-08-20 second revision, actually sent to oshpark
2016-08-20 tried to add sma connector in addition to ufl, not happy w/it
2016-08-20 new feather wing designed to have gps mod plug in
2016-08-20 fix silkscreen issue on previous revision
2016-09-07 change to gps module again
2016-09-07 change to gps module again: the rest of it
2016-12-28 initial work for tricorder pi head cover
2016-12-30 initial checkin of teensy version
2017-01-03 rearrange display
2017-01-03 more display wankery
2017-01-03 notes jotted down for laying out display
2017-01-03 move docs up a level
2017-01-03 saving for later
2017-01-03 remove display buffer for now to focus on sensors
2017-01-03 dump extraneous code
2017-01-04 old color info
2017-01-04 WIP sorta working if you look at it sideways (literally, the x & y axes are flipped for the font)
2017-01-05 wip new hardware for dedicated teensy 3.2 hat
2017-01-06 wip teensy hat layout
2017-01-10 gas sensor test boards
2017-01-10 rev1.8 of tricorder hat, now for teensy:
2017-01-10 rework teensy hat so it only requires single row smt header
2017-01-25 adding battery gauge
2017-01-25 layout complete
2017-01-25 silkscreen fix because of course
2017-11-08 disconnect gps from UART0
2017-11-08 remove sleep because wat
2018-10-26 no longer needed header file
2018-10-26 planning screen layout again
2019-02-25 wip new board rev
2019-02-25 wip spectrometer stuff
2019-03-01 new revision with LTC2942 instead of '41
2019-03-04 more cleanup
2019-03-05 commenting out GPS stuff for now
2019-03-23 attempting to better secure GPS board
2019-03-23 yet another poss revision for RTC batter
2019-03-23 Teensy RTC enabled, switched GPS libs
2019-10-04 remove adafruit gps lib stuff
2019-10-04 switched out 9DoF sensors

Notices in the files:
parts and their libraries:
A_butts: Released under the Creative Commons Attribution Share-Alike 4.0 License
A_butts: https://creativecommons.org/licenses/by-sa/4.0
A_butts: Released under the Creative Commons
